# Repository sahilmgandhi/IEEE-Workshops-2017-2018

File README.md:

# IEEE_Workshops_2017_2018

Code base, powerpoints, and other materials for the IEEE 2017 to 2018 Workshop year.

# Lab Tools and Debugging Workshop

The powerpoint for the workshop is available in the folder.

# Through-Hole Soldering Workshop

The powerpoint as well as the .elf and .hex files are avaiable in the folder to program the MCU.

To program the ATMEGA-328, you can use a program like avrdude or even the Arduino IDE with an appropriate
programmer. You can also use another Arduino (like an Uno or a Nano) as a programmer for the ATMEGA-328.

# Eagle Workshop

The schematic that we used and the PCB that we created from it are available in this folder.

# Android + Bluetooth Workshop

### Instructions to Use:

    Bluetooth -> Arduino

For the AT-commands for the HC-05 Bluetooth Module, start both the BluetoothSerial and regular
Serial Monitor at a baud rate of 38400. Additionally, the EN pin must be set to HIGH (attach it
to the 3.3V line for the Arduino Nano), and the button on the HC-05 must be pressed as well while 
powering the device. Once the device is on, the button can be released, and the AT-commands will go through. 

After the AT-commands of choice have been coded, change the Baud rate of both Serial modes to 9600
for normal interaction with your Android application.

For other bluetooth modules, the Baud rate for the AT-mode and regular use mode might be different, 
and there may be other modes (not AT) to program the bluetooth module.

    Bluetooth -> Android

Turn on bluetooth on your Android device. Find the Bluetooth device with the name that you set up with 
the AT-commands. Connect to the device, and then open up the application. Remember to make sure the Baud rate
on the Arduino is set to 9600 (if you are using the HC-05) in order to properly send and receive data from your
Android device.

# 3D_Printing 

The powerpoint as well as the 3D printing guide to making objects for the lab's Dreammaker printer are available in this folder.

# Advanced MCU Workshop

The powerpoint and the code that we went over is available in this folder.

# SMD Soldering

The schematic and board that we used for this workshop are available in this folder.

# SPI Communication Workshop

The code we went over along with the powerpoint presentation are available in this folder. 

# TI Microcontroller

In this workshop, we use the MSP432P401R Launchpad from Texas Instruments. In our presentation, we included a simple project that allows you to use the launchpad to control the ultrasonic distance sensor. The serial port will print the sensor's distance to the object it is directly facing. You can find the original code in the DistanceSensor_code file.

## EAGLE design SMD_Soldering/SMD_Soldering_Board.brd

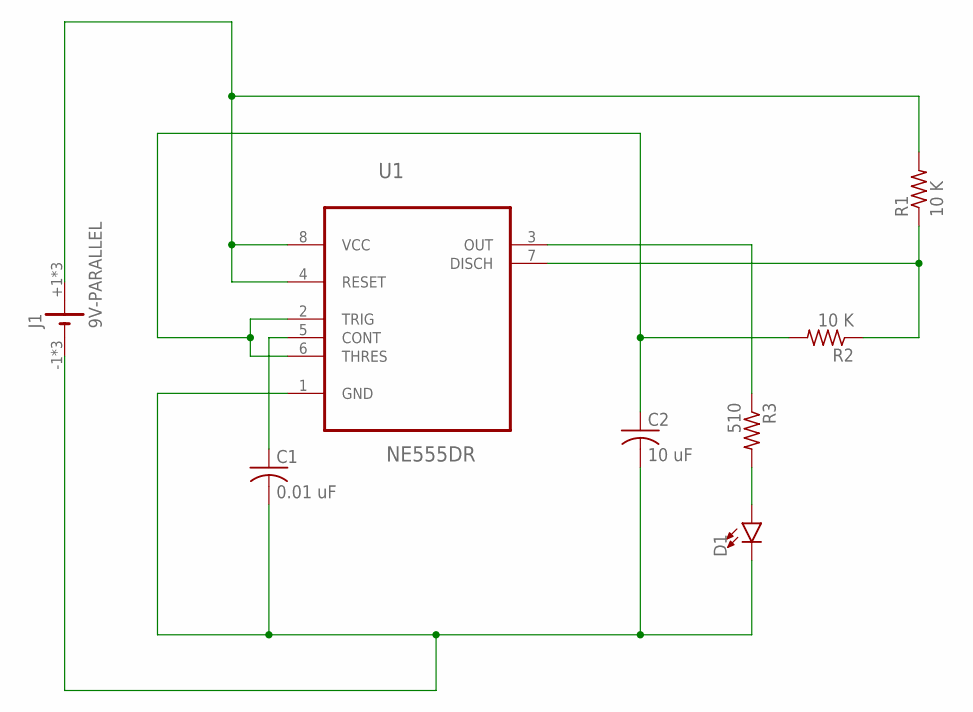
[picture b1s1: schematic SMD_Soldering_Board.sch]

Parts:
C1: 0.01 uF; C0603
C2: 10 uF; C0603
D1: LED0603; LED-0603
J1: 9V-PARALLEL; 9V-PARALLEL-CLIP
R1, R2: 10 K; R0603
R3: 510; R0603
U1: NE555DR; SOIC127P600X175-8N

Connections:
9V: J1.+1 (+), J1.+2 (+), J1.+3 (+), R1.2, U1.4 (RESET), U1.8 (VCC)
GND: C1.2, C2.2, D1.C, J1.-1 (-), J1.-2 (-), J1.-3 (-), U1.1 (GND)
unnamed: C2.1, R2.2, U1.2 (TRIG), U1.6 (THRES)
unnamed: R1.1, R2.1, U1.7 (DISCH)
unnamed: R3.1, U1.3 (OUT)
unnamed: C1.1, U1.5 (CONT)
unnamed: D1.A, R3.2

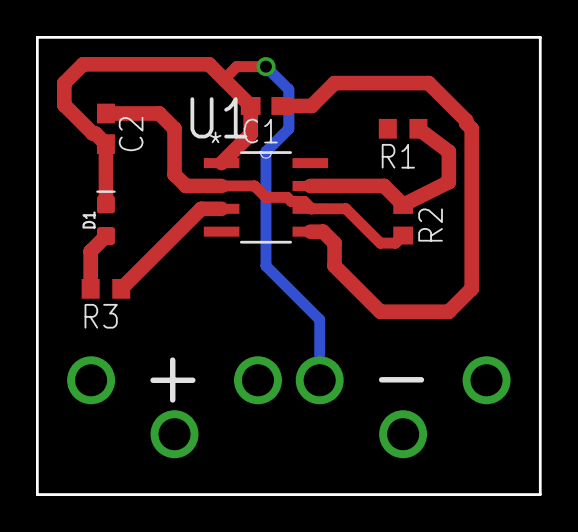
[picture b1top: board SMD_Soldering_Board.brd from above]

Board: 2 copper layers, 27.9 x 25.4 mm, 8 parts (0 on the bottom side), 7 nets.

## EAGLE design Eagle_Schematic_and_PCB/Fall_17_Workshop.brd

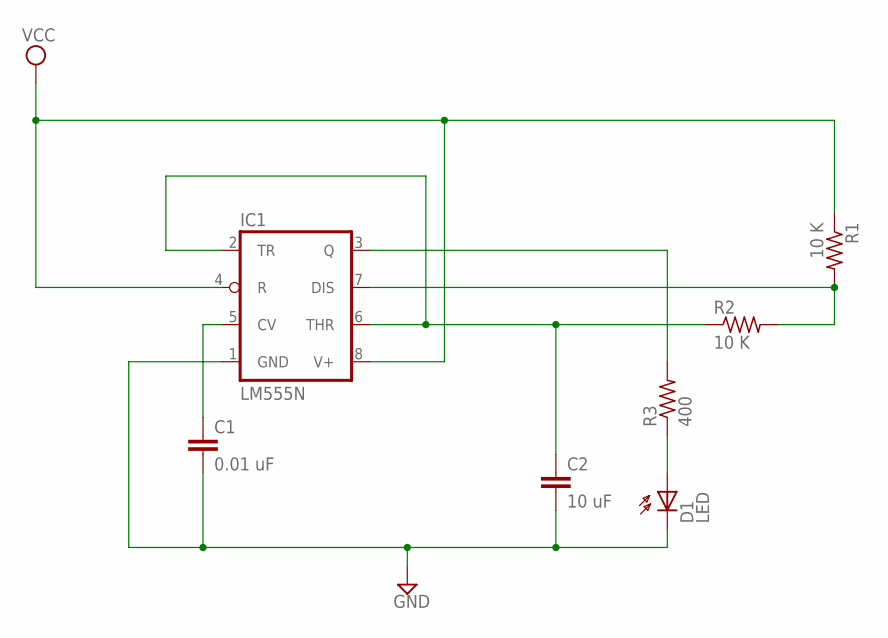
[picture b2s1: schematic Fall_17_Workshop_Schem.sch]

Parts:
C1: 0.01 uF; C5B2.5
C2: 10 uF; C5B2.5
D1: LED; SFH205
IC1: LM555N; DIL08
R1, R2: 10 K; 0204/7
R3: 400; 0204/7

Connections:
GND: C1.2, C2.2, D1.K (C), IC1.1 (GND)
unnamed: C1.1, IC1.5 (CV)
unnamed: C2.1, IC1.2 (TR), IC1.6 (THR), R2.1
unnamed: IC1.7 (DIS), R1.2, R2.2
unnamed: IC1.3 (Q), R3.2
unnamed: D1.A, R3.1
VCC: IC1.4 (R), IC1.8 (V+), R1.1

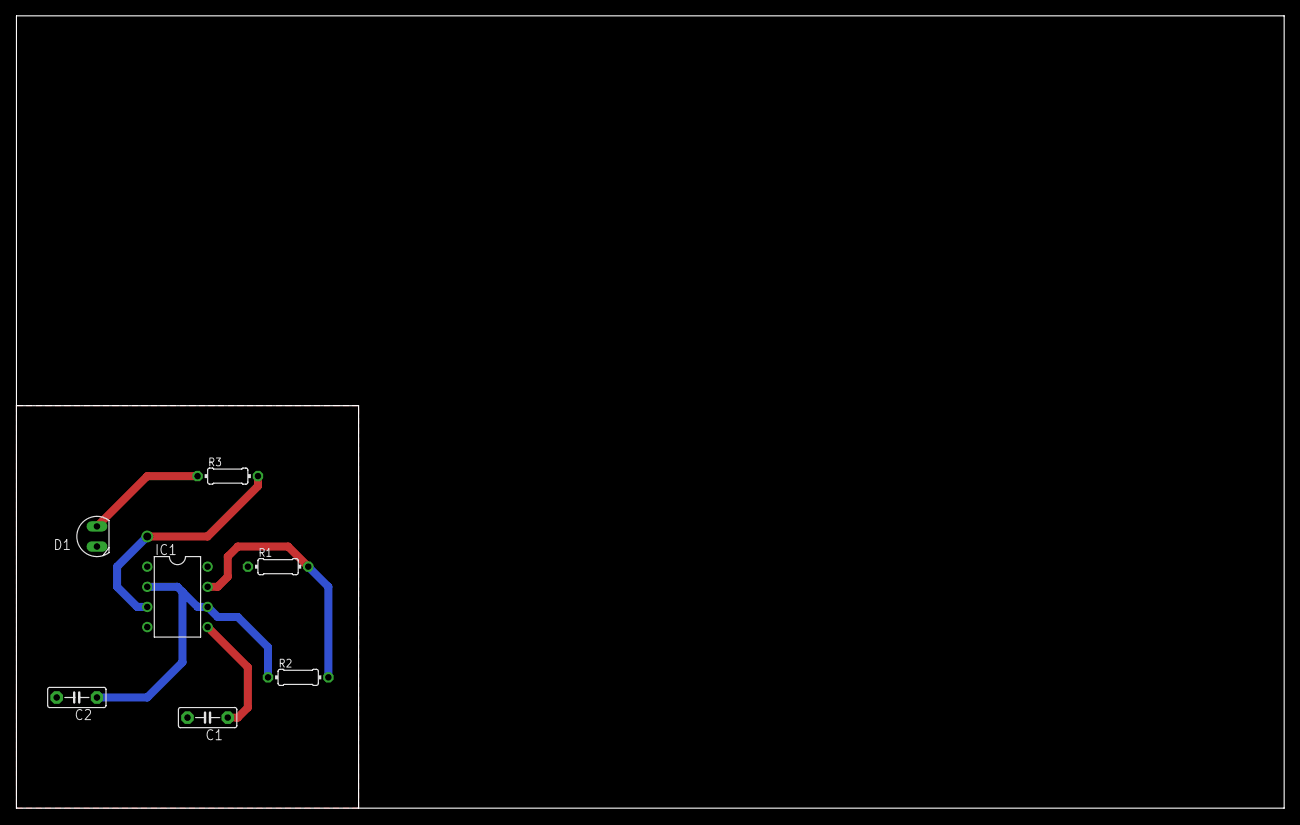
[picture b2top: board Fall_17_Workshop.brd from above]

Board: 2 copper layers, 160.0 x 100.0 mm, 7 parts (0 on the bottom side), 7 nets.

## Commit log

2017-07-10 Code drop
    Added arduino and Android Code
2017-07-11 Updating README
2017-07-11 Updated readme for bluetooth with the arduino
2017-07-23 Updated readme for the android and bluetooth workshop
2017-11-02 Add soldering and debugging workshop. Update readme
2017-11-11 Add initial eagle schematic
2017-11-11 Create license
2017-11-11 Create Code of conduct
2017-11-11 Finish eagle schematic and pcb
2017-11-11 rename pcb files
2017-11-11 Add useful libraries for Eagle
2017-12-02 Add javadoc docmments and portrait only option
2017-12-02 Update comment and code structure for Arduino Code
2017-12-05 Update arduino bluetooth
2018-01-09 Add initial SMD Soldering pcb
2018-01-13 Update Bluetooth Errors
2018-01-14 Start MCU_GPIO code
2018-01-16 Update brd and add gitignore
2018-01-21 Create Advanced_MCU
2018-01-21 Create mcu_analogInput
2018-02-01 Add gear object
2018-02-07 Add instructions for lab printer
2018-03-11 Update readme and add SPI file structure
2018-04-20 Create DistanceSensor_code
2018-04-25 Create Counter_code
2020-04-03 Update project settings

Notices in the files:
parts and their libraries:
SparkFun-LED: Licensing: Creative Commons ShareAlike 4.0 International - https://creativecommons.org/licenses/by-sa/4.0
